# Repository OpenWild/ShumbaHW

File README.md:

# ShumbaHW
Shumba Bioacoustic Monitoring Hardware

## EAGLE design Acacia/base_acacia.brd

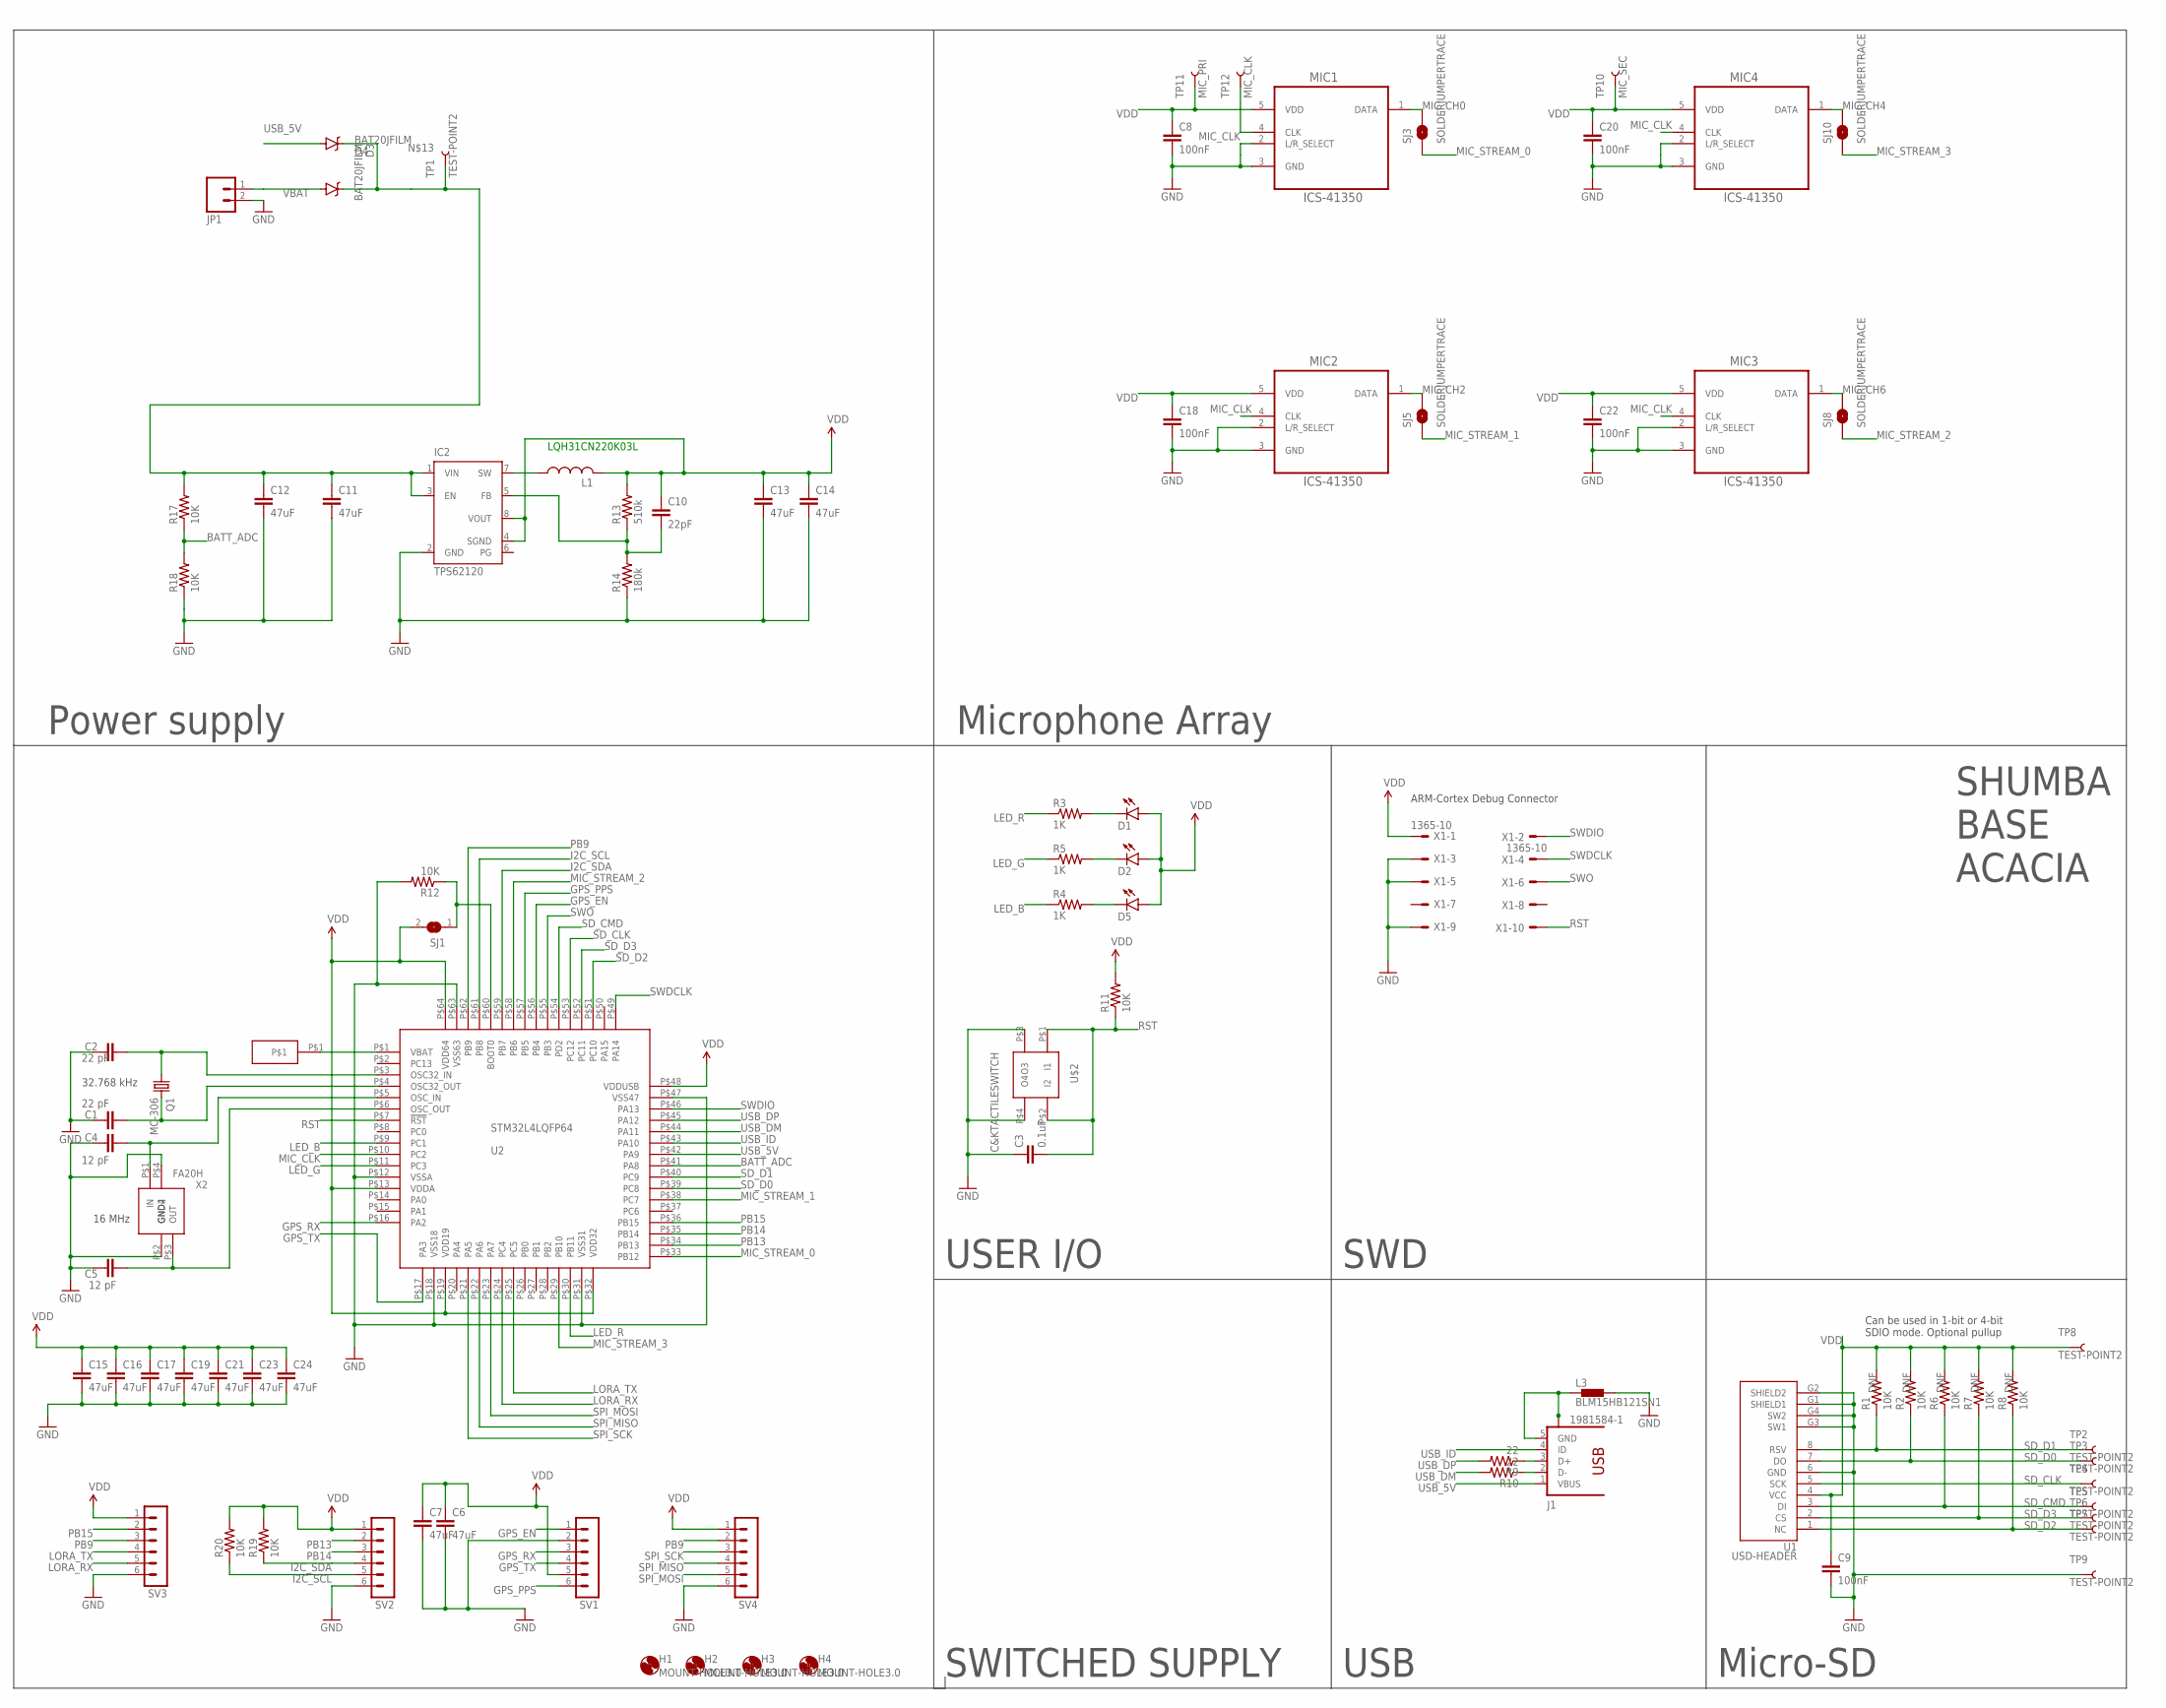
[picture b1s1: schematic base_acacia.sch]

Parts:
C1, C2: 22 pF; 0603-CAP
C3: 0.1uF; 0603-CAP
C4, C5: 12 pF; 0603-CAP
C6, C7, C11, C12, C13, C14, C15, C16, C17, C19, C21, C23, C24: 47uF; 0603-CAP
C8, C9, C18, C20, C22: 100nF; 0603-CAP
C10: 22pF; 0603-CAP
D1, D2, D5: LED0603; LED-0603
D3, D4: BAT20JFILM; SOD-323
H1, H2, H3, H4: MOUNT-HOLE3.0; 3,0
IC2: TPS62120; DCN-R-PDSO-G8
J1: 1981584-1; MPN ZX 62 B 5PA(33)
JP1: M02PTH4; 1X02_XTRA_BIG
L1: L-USL3216C; L3216C
L3: BLM15HB121SN1; 0402
MIC1, MIC2, MIC3, MIC4: ICS-41350; ADI_ADMP521A
Q1: MC-306; MPN MC-306 32.768KHZ 20PPM ,12.5PF
R1, R2, R6, R7, R8, R11, R12, R17, R18, R19, R20: 10K; 0603-RES
R3, R4, R5: 1K; 0603-RES
R9, R10: 22; 0603-RES
R13: 510k; 0603-RES
R14: 180k; 0603-RES
SJ1: SJ
SJ3, SJ5, SJ8, SJ10: SOLDERJUMPERTRACE; SJ_2S-TRACE
SV1, SV2, SV3, SV4: MA06-1
TP1, TP2, TP3, TP4, TP5, TP6, TP7, TP8, TP9: TEST-POINT2; PAD.02X.02
TP10: MIC_SEC; PAD.02X.02
TP11: MIC_PRI; PAD.02X.02
TP12: MIC_CLK; PAD.02X.02
U1: USD-HEADER; USD-HEADER-1.1
U2: STM32L4LQFP64
U$2: C&KTACTILESWITCH
U$7: SMDPAD
X1: 1365-10
X2: FA20H; FA-20H; MPN Q24FA20H00044 FA-20H 16 MHZ 9.0PF Cryst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

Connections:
BATT_ADC: R17.1, R18.2, U2.P$41 (PA8)
GND: C1.1, C2.1, C3.1, C4.1, C5.1, C6.2, C7.2, C8.2, C9.2, C11.2, C12.2, C13.2, C14.2, C15.2, C16.2, C17.2, C18.2, C19.2, C20.2, C21.2, C22.2, C23.2, C24.2, IC2.2 (GND), JP1.2, L3.2, MIC1.2 (L/R_SELECT), MIC1.3 (GND), MIC2.2 (L/R_SELECT), MIC2.3 (GND), MIC3.2 (L/R_SELECT), MIC3.3 (GND), MIC4.2 (L/R_SELECT), MIC4.3 (GND), R12.2, R14.1, R18.1, SV1.2, SV2.6, SV3.6, SV4.6, TP9.P$1, U1.6 (GND), U1.G1 (SHIELD1), U1.G2 (SHIELD2), U1.G3 (SW1), U1.G4 (SW2), U2.P$12 (VSSA), U2.P$18 (VSS18), U2.P$31 (VSS31), U2.P$47 (VSS47), U2.P$63 (VSS63), U$2.P$3 (O3), U$2.P$4 (O4), X1.3, X1.5, X1.9, X2.P$2 (GND2), X2.P$4 (GND4)
GPS_EN: SV1.1, U2.P$56 (PB4)
GPS_PPS: SV1.6, U2.P$57 (PB5)
GPS_RX: SV1.3, U2.P$16 (PA2)
GPS_TX: SV1.4, U2.P$17 (PA3)
I2C_SCL: R20.1, SV2.5, U2.P$61 (PB8)
I2C_SDA: R19.1, SV2.4, U2.P$59 (PB7)
LED_B: R4.1, U2.P$9 (PC1)
LED_G: R5.1, U2.P$11 (PC3)
LED_R: R3.1, U2.P$30 (PB11)
LORA_RX: SV3.5, U2.P$24 (PC4)
LORA_TX: SV3.4, U2.P$25 (PC5)
MIC_CH0: MIC1.1 (DATA), SJ3.2
MIC_CH2: MIC2.1 (DATA), SJ5.2
MIC_CH4: MIC4.1 (DATA), SJ10.2
MIC_CH6: MIC3.1 (DATA), SJ8.2
MIC_CLK: MIC1.4 (CLK), MIC2.4 (CLK), MIC3.4 (CLK), MIC4.4 (CLK), TP12.P$1, U2.P$10 (PC2)
MIC_STREAM_0: SJ3.1, U2.P$33 (PB12)
MIC_STREAM_1: SJ5.1, U2.P$38 (PC7)
MIC_STREAM_2: SJ8.1, U2.P$58 (PB6)
MIC_STREAM_3: SJ10.1, U2.P$29 (PB10)
unnamed: C2.2, Q1.1, U2.P$3 (OSC32_IN)
unnamed: C1.2, Q1.4 (2), U2.P$4 (OSC32_OUT)
unnamed: C4.2, U2.P$5 (OSC_IN), X2.P$1 (IN)
unnamed: C5.2, U2.P$6 (OSC_OUT), X2.P$3 (OUT)
unnamed: J1.3 (D+), R9.1
unnamed: R12.1, SJ1.1, U2.P$60 (BOOT0)
unnamed: J1.2 (D-), R10.1
unnamed: U2.P$1 (VBAT), U$7.P$1
unnamed: D1.C, R3.2
unnamed: D2.C, R5.2
unnamed: C11.1, C12.1, D3.C, D4.C, IC2.1 (VIN), IC2.3 (EN), R17.2, TP1.P$1
unnamed: D5.C, R4.2
unnamed: IC2.7 (SW), L1.1
unnamed: C10.2, IC2.5 (FB), R13.1, R14.2
PB9: SV3.3, SV4.2, U2.P$62 (PB9)
PB13: SV2.2, U2.P$34 (PB13)
PB14: SV2.3, U2.P$35 (PB14)
PB15: SV3.2, U2.P$36 (PB15)
RST: C3.2, R11.1, U2.P$7 (!RST), U$2.P$1 (I1), U$2.P$2 (I2), X1.10
SD_CLK: TP4.P$1, U1.5 (SCK), U2.P$53 (PC12)
SD_CMD: R6.1, TP5.P$1, U1.3 (DI), U2.P$54 (PD2)
SD_D0: R2.1, TP3.P$1, U1.7 (DO), U2.P$39 (PC8)
SD_D1: R1.1, TP2.P$1, U1.8 (RSV), U2.P$40 (PC9)
SD_D2: R8.1, TP7.P$1, U1.1 (NC), U2.P$51 (PC10)
SD_D3: R7.1, TP6.P$1, U1.2 (CS), U2.P$52 (PC11)
SPI_MISO: SV4.4, U2.P$22 (PA6)
SPI_MOSI: SV4.5, U2.P$23 (PA7)
SPI_SCK: SV4.3, U2.P$21 (PA5)
SWDCLK: U2.P$49 (PA14), X1.4
SWDIO: U2.P$46 (PA13), X1.2
SWO: U2.P$55 (PB3), X1.6
USB_5V: D4.A, J1.1 (VBUS), U2.P$42 (PA9)
USB_DM: R10.2, U2.P$44 (PA11)
USB_DP: R9.2, U2.P$45 (PA12)
USB_ID: J1.4 (ID), U2.P$43 (PA10)
USB_SHIELD: J1.5 (GND), J1.S1, J1.S2, J1.S3, J1.S4, L3.1
VBAT: D3.A, JP1.1
VDD: C6.1, C7.1, C8.1, C9.1, C10.1, C13.1, C14.1, C15.1, C16.1, C17.1, C18.1, C19.1, C20.1, C21.1, C22.1, C23.1, C24.1, D1.A, D2.A, D5.A, IC2.4 (SGND), IC2.8 (VOUT), L1.2, MIC1.5 (VDD), MIC2.5 (VDD), MIC3.5 (VDD), MIC4.5 (VDD), R1.2, R2.2, R6.2, R7.2, R8.2, R11.2, R13.2, R19.2, R20.2, SJ1.2, SV1.5, SV2.1, SV3.1, SV4.1, TP8.P$1, TP10.P$1, TP11.P$1, U1.4 (VCC), U2.P$13 (VDDA), U2.P$19 (VDD19), U2.P$32 (VDD32), U2.P$48 (VDDUSB), U2.P$64 (VDD64), X1.1

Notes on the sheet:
ARM-Cortex Debug Connector
Power supply
Micro-SD
Can be used in 1-bit or 4-bit SDIO mode. Optional pullup
USB
SWD
USER I/O
Microphone Array
32.768 kHz
16 MHz
SWITCHED SUPPLY
LQH31CN220K03L
SHUMBA BASE ACACIA

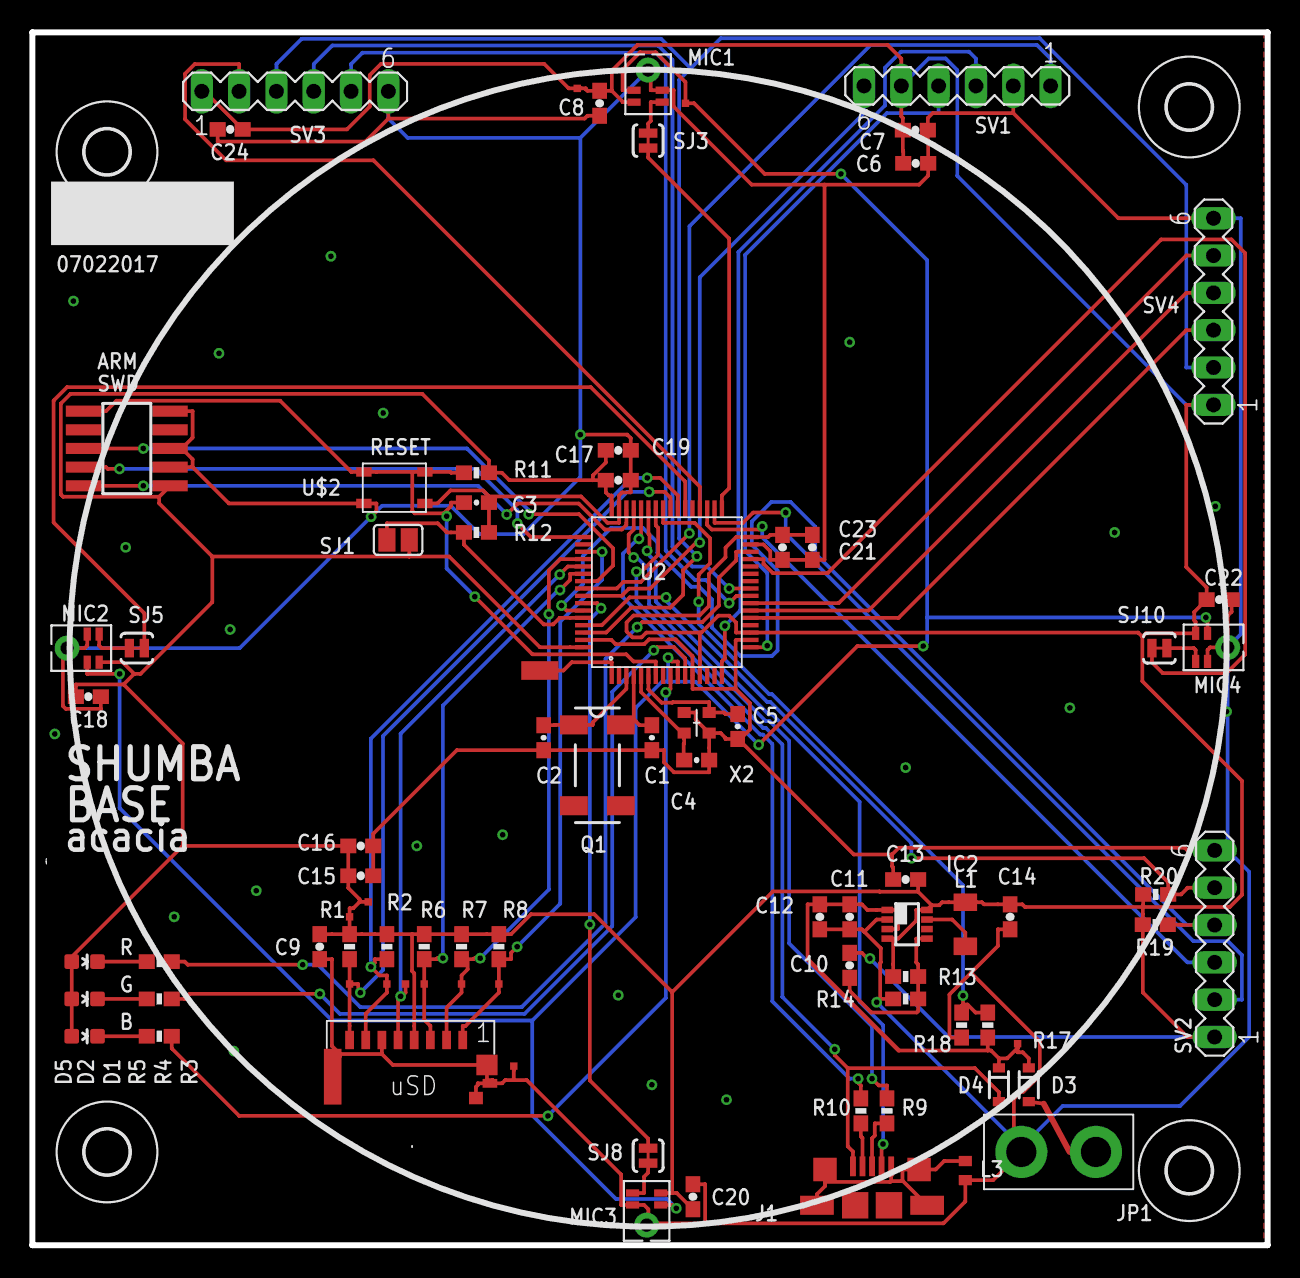
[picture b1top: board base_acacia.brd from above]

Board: 2 copper layers, 84.1 x 82.5 mm, 88 parts (0 on the bottom side), 60 nets.

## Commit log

2019-10-03 Initial Commit of Acacia PCB

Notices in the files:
parts and their libraries:
SparkFun-Capacitors: Licensing: Creative Commons ShareAlike 4.0 International - https://creativecommons.org/licenses/by-sa/4.0
con-usb: Copyright (C) 2008, Bob Starr
